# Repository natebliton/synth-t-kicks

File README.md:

# synth-t-kicks
t-bridge synth kick drum and tom versions

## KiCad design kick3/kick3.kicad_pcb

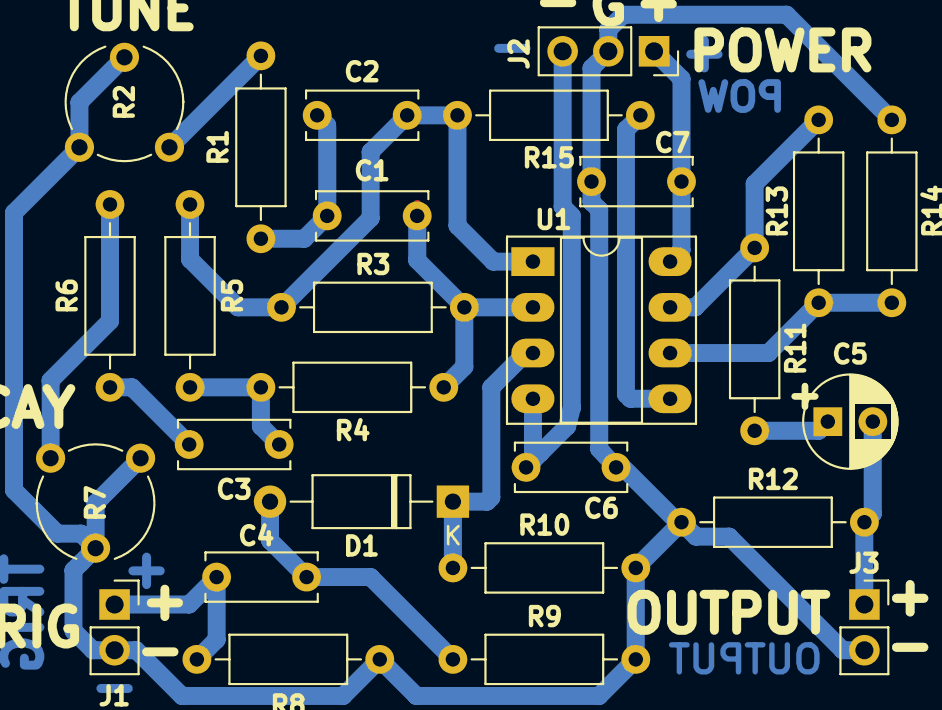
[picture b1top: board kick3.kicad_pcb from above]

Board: 2 copper layers, 27 parts (0 on the bottom side), 18 nets.

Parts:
C1, C2, C3, C4: 100nF; C_Disc_D6.0mm_W2.5mm_P5.00mm
C5: 10uF; CP_Radial_D5.0mm_P2.50mm
C6, C7: 100pF; C_Disc_D6.0mm_W2.5mm_P5.00mm
D1: 1N4148; D_A-405_P10.16mm_Horizontal
J1: Input; PinSocket_1x02_P2.54mm_Vertical
J2: Power; PinSocket_1x03_P2.54mm_Vertical
J3: Output; PinSocket_1x02_P2.54mm_Vertical
R1, R6: 220; R_Axial_DIN0207_L6.3mm_D2.5mm_P10.16mm_Horizontal
R2: 10k; Potentiometer_Piher_PT-6-V_Vertical
R3: 1M; R_Axial_DIN0207_L6.3mm_D2.5mm_P10.16mm_Horizontal
R4, R5, R12: 470k; R_Axial_DIN0207_L6.3mm_D2.5mm_P10.16mm_Horizontal
R7: 100k; Potentiometer_Piher_PT-6-V_Vertical
R8, R9, R10: 10k; R_Axial_DIN0207_L6.3mm_D2.5mm_P10.16mm_Horizontal
R11: 4.7k; R_Axial_DIN0207_L6.3mm_D2.5mm_P10.16mm_Horizontal
R13, R14: 1K; R_Axial_DIN0207_L6.3mm_D2.5mm_P10.16mm_Horizontal
R15: 1k; R_Axial_DIN0207_L6.3mm_D2.5mm_P10.16mm_Horizontal
U1: TL072; DIP-8_W7.62mm_Socket_LongPads

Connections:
GND: C6.2, C7.2, J1.2, J2.2, J3.2, R2.2, R2.3, R7.2, R7.3, R8.2, R9.2, R10.2, R12.1, R14.2
unnamed: C1.1, C2.2, R1.1
unnamed: C1.2, R3.2, R4.2, U1.2
unnamed: C2.1, R3.1, R5.1, R15.2, U1.1
unnamed: C3.1, R4.1, R5.2
unnamed: C3.2, R6.1
unnamed: C4.1, D1.2, R9.1
unnamed: C4.2, J1.1, R8.1
unnamed: C5.1, R11.1
unnamed: C5.2, J3.1, R12.2
unnamed: C6.1, J2.3, U1.4
unnamed: C7.1, J2.1, U1.8
unnamed: D1.1, R10.1, U1.3
unnamed: R1.2, R2.1
unnamed: R6.2, R7.1
unnamed: R11.2, R13.1, U1.7
unnamed: R13.2, R14.1, U1.6
unnamed: R15.1, U1.5

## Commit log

2020-11-28 initial commit, and starting v3
